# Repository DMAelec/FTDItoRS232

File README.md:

# FTDItoRS232
An FTDI based USB to RS232 adapter that has a USB type A plug. This adapter has all the control signals wired up(RTS,CTS,DSR,DTR,CD,RI) with
pin 9(RI) on the DB-9 connector always active during standby.

This adapter is designed with KiCad ver 5.1 and has the gerbers located in the GERBER.zip folder. The bill of materials which contains
the part values and Digikey/Mouser part numbers are located in the BOM.txt file.

NOTE: It is recommended to use a PCB vendor that can produce 1.2mm boards in order to properly fit the DB-9 connector.
ALSO NOTE: This project utilizes mostly SMD parts and is for people with proper skills and tools for working with SMD.

Current Revision #2

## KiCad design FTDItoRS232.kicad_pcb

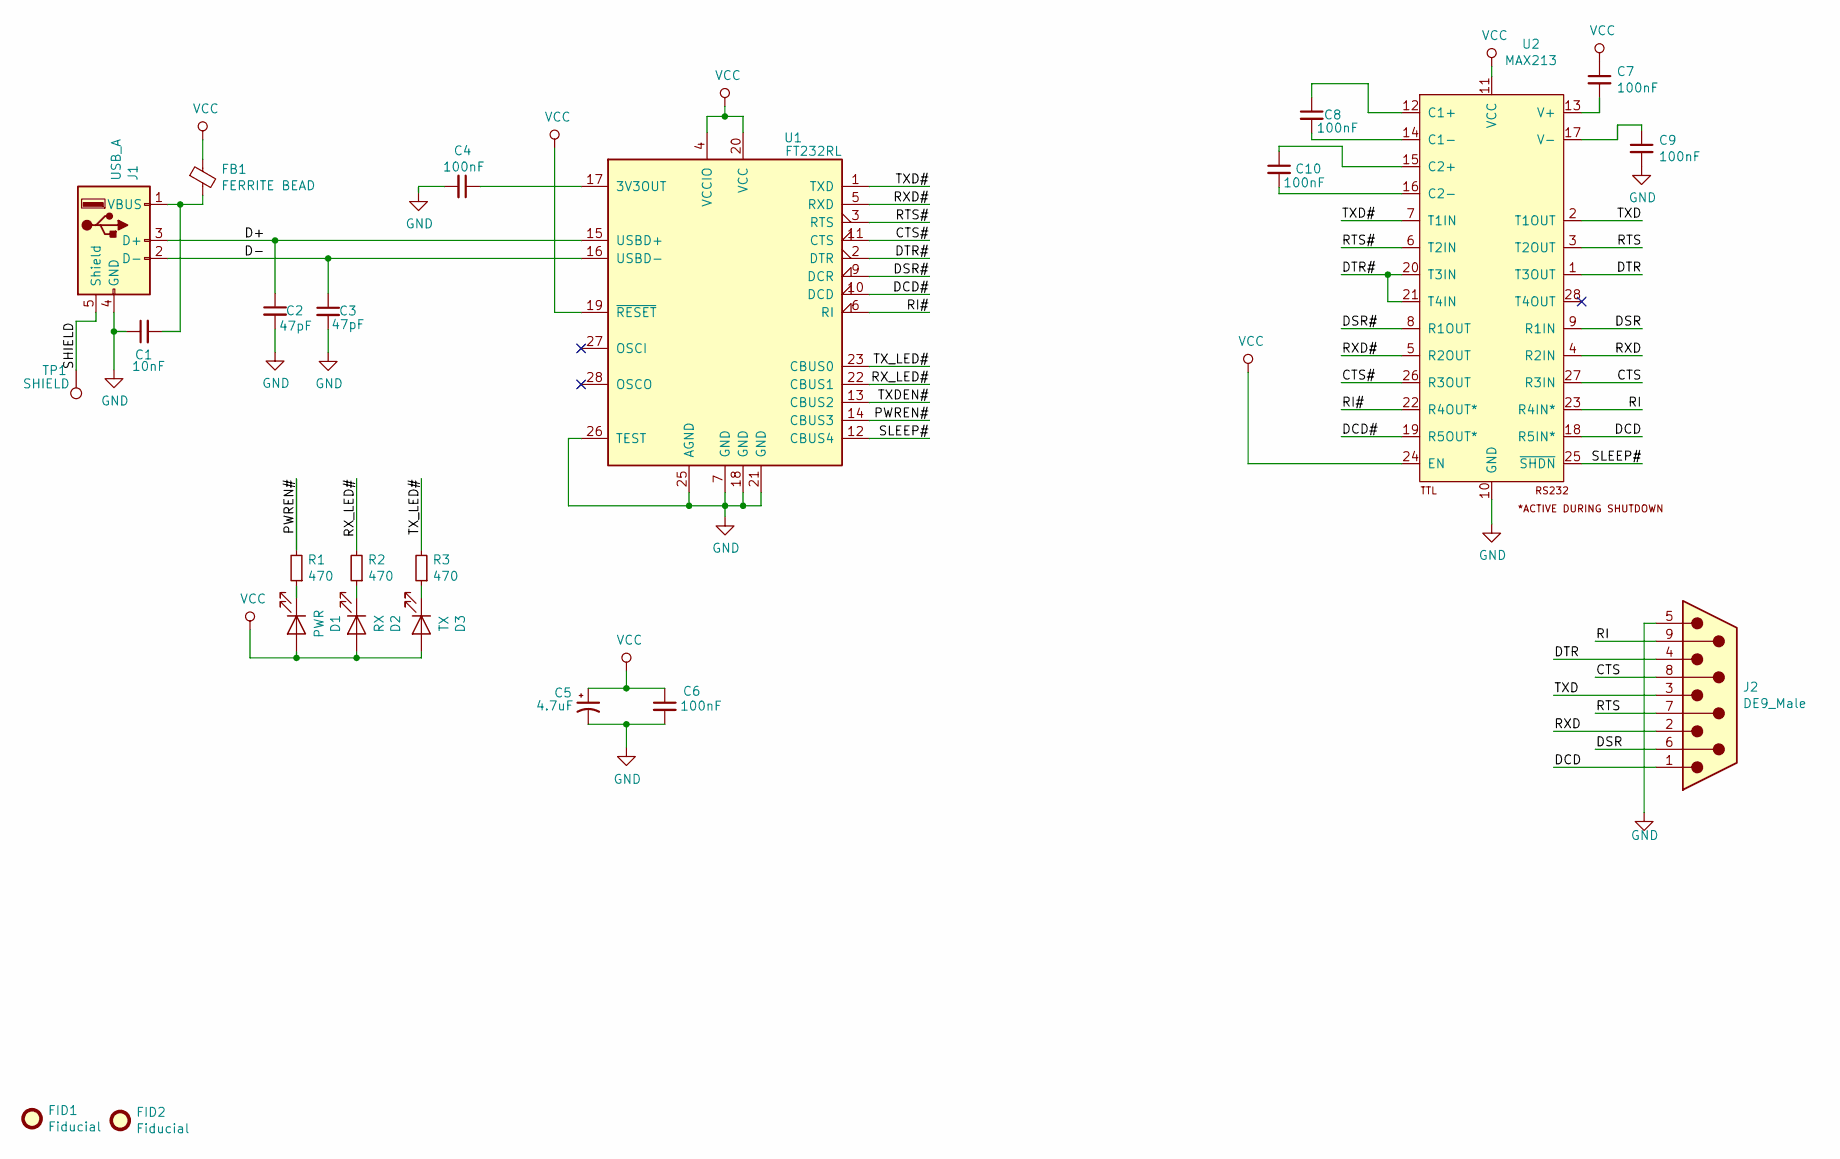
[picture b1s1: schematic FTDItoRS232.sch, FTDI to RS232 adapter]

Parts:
C1: 10nF; C_0603_1608Metric
C2, C3: 47pF; C_0603_1608Metric
C4, C6, C7, C8, C9, C10: 100nF; C_0603_1608Metric
C5: 4.7uF; CP_EIA-3216-18_Kemet-A
D1: PWR; LED_0805_2012Metric
D2: RX; LED_0805_2012Metric
D3: TX; LED_0805_2012Metric
FB1: FERRITE BEAD; L_0805_2012Metric_Pad1.15x1.40mm_HandSolder
FID1, FID2: Fiducial; Fiducial_1mm_Mask2mm
J1: USB_A; USB_A_Plug_Horizontal
J2: DE9_Male; DSUB-9_Male_EdgeMount_P2.77mm
R1, R2, R3: 470; R_0603_1608Metric
TP1: SHIELD; TestPoint_THTPad_1.0x1.0mm_Drill0.5mm
U1: FT232RL; SSOP-28_5.3x10.2mm_P0.65mm
U2: MAX213; SSOP-28_5.3x10.2mm_P0.65mm

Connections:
/CTS: J2.8, U2.27 (R3IN)
/CTS#: U1.11 (CTS), U2.26 (R3OUT)
/D+: C2.1, J1.3 (D+), U1.15 (USBD+)
/D-: C3.1, J1.2 (D-), U1.16 (USBD-)
/DCD: J2.1, U2.18 (R5IN*)
/DCD#: U1.10 (DCD), U2.19 (R5OUT*)
/DSR: J2.6, U2.9 (R1IN)
/DSR#: U1.9 (DCR), U2.8 (R1OUT)
/DTR: J2.4, U2.1 (T3OUT)
/DTR#: U1.2 (DTR), U2.20 (T3IN), U2.21 (T4IN)
/PWREN#: R1.2, U1.14 (CBUS3)
/RI: J2.9, U2.23 (R4IN*)
/RI#: U1.6 (RI), U2.22 (R4OUT*)
/RTS: J2.7, U2.3 (T2OUT)
/RTS#: U1.3 (RTS), U2.6 (T2IN)
/RXD: J2.2, U2.4 (R2IN)
/RXD#: U1.5 (RXD), U2.5 (R2OUT)
/RX_LED#: R2.2, U1.22 (CBUS1)
/SHIELD: J1.5 (Shield), TP1.1
/SLEEP#: U1.12 (CBUS4), U2.25 (~SHDN)
/TXD: J2.3, U2.2 (T1OUT)
/TXD#: U1.1 (TXD), U2.7 (T1IN)
/TXDEN#: U1.13 (CBUS2)
/TX_LED#: R3.2, U1.23 (CBUS0)
GND: C1.1, C2.2, C3.2, C4.2, C5.2, C6.2, C9.2, J1.4 (GND), J2.5, U1.7 (GND), U1.18 (GND), U1.21 (GND), U1.25 (AGND), U1.26 (TEST), U2.10 (GND)
unnamed: C1.2, FB1.2, J1.1 (VBUS)
unnamed: C4.1, U1.17 (3V3OUT)
unnamed: C7.2, U2.13 (V+)
unnamed: C8.1, U2.12 (C1+)
unnamed: C8.2, U2.14 (C1-)
unnamed: C9.1, U2.17 (V-)
unnamed: C10.1, U2.15 (C2+)
unnamed: C10.2, U2.16 (C2-)
unnamed: D1.1 (K), R1.1
unnamed: D2.1 (K), R2.1
unnamed: D3.1 (K), R3.1
VCC: C5.1, C6.1, C7.1, D1.2 (A), D2.2 (A), D3.2 (A), FB1.1, U1.4 (VCCIO), U1.19 (~RESET~), U1.20 (VCC), U2.11 (VCC), U2.24 (EN)

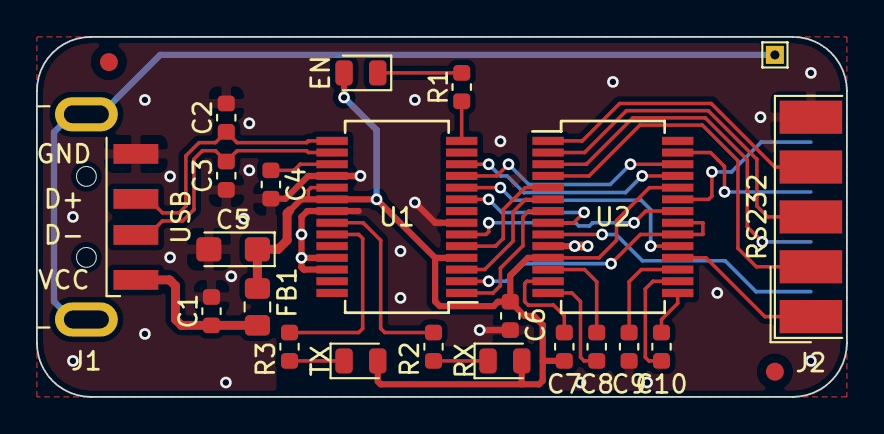
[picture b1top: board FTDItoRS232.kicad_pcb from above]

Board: 2 copper layers, 45.0 x 20.0 mm, 24 parts (0 on the bottom side), 36 nets.

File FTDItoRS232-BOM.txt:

REF			VALUE			PART NO.
----------------------------------------------------------------------
R1,R2,R3		470 Ohm			CRCW0603470RJNEAC


D1			LED GREEN		VFHD1112H-3B72B-TR


D2,D3			LED YELLOW		VFHY1112H-3BY2D-TR


C1			10nF CERAMIC		C0603C103J4RACTU


C2,C3			47pF CERAMIC		C0603C470F5GAC7411


C4,C6,C7,		100nF CERAMIC		C0603C104J4RAC7040
C8,C9,C10


C5			4.7uF TANTALUM		T491A475K010AT


FB1			220 Ohm FERRITE BEAD	BLM21BB221SN1D


Y1(REV 1)		12MHz CRYSTAL		445I32E12M00000


U1			FT232RL			FT232RL-REEL


U2			MAX213			SP213EHCA-L/TR


J1			CONN USB TYPE-A		1734028-1


J2			CONN DE9 MALE		5-747904-5

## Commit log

2023-01-18 Added readme
